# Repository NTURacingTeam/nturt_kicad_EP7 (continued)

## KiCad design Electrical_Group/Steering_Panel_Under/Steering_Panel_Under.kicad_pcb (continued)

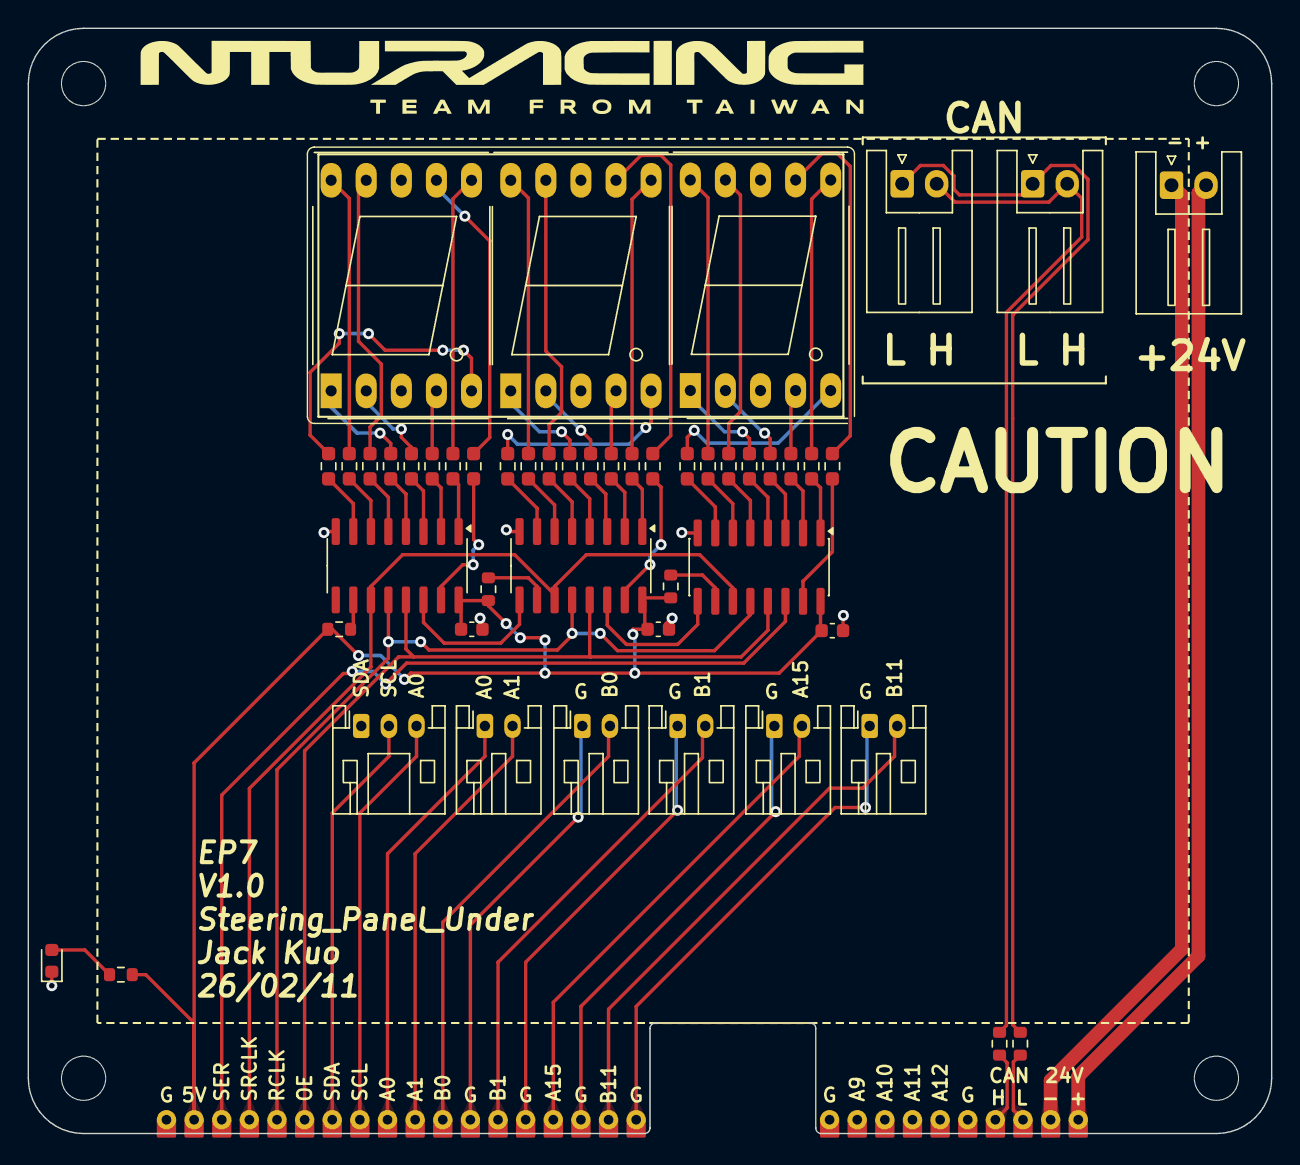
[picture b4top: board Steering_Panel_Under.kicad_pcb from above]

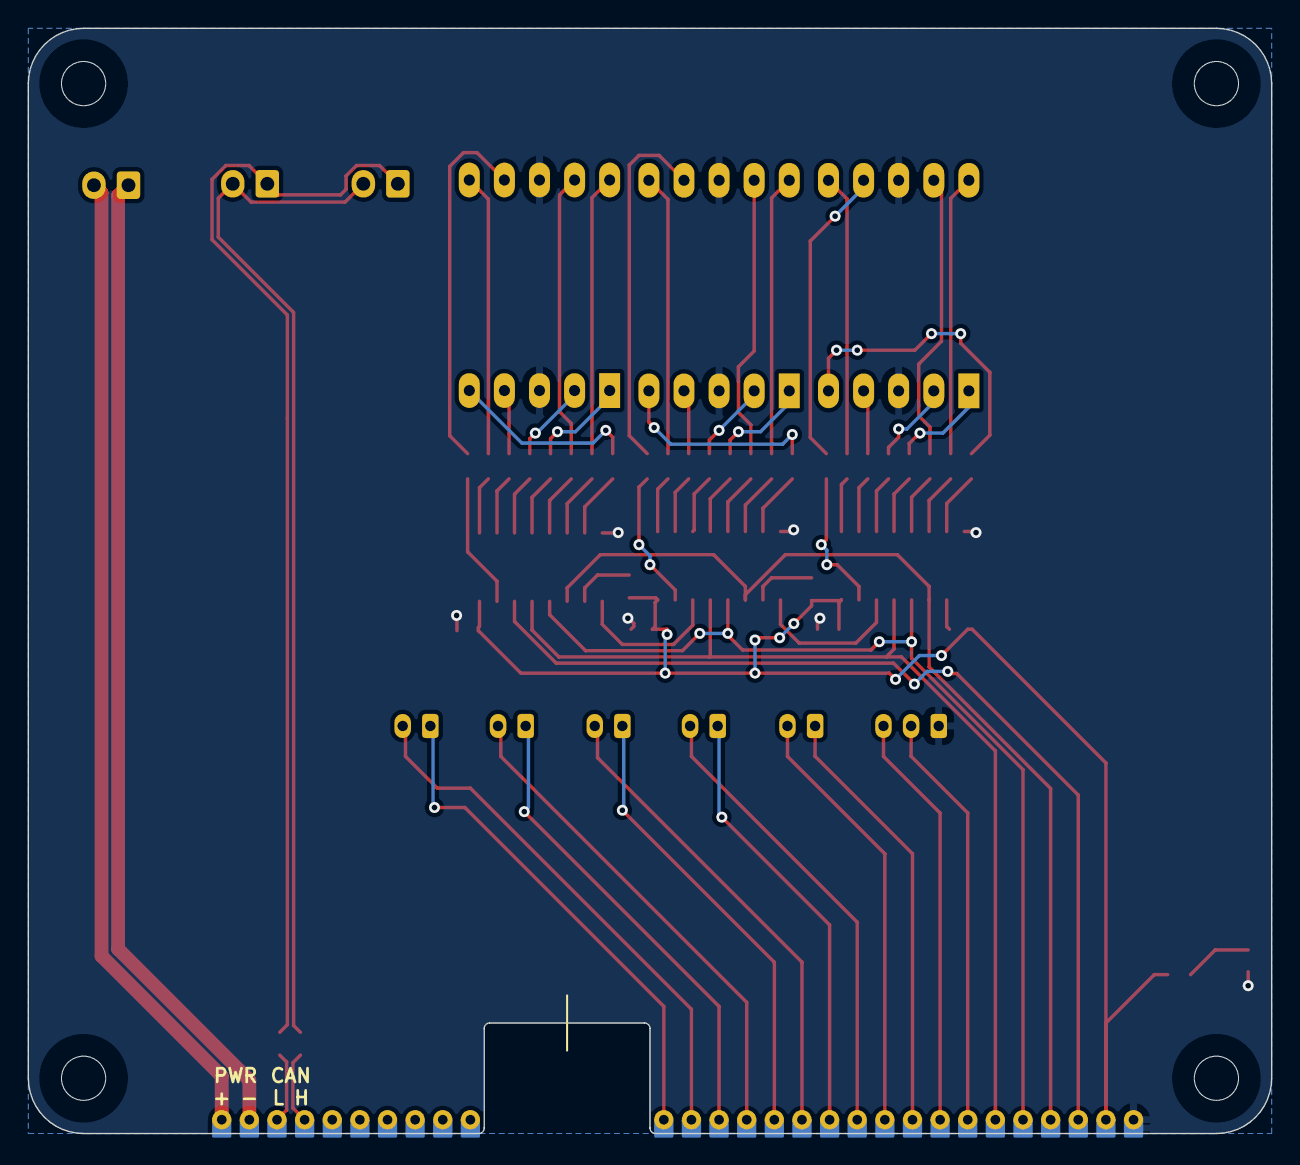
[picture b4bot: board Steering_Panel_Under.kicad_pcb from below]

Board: 2 copper layers, 90.0 x 80.0 mm, 81 parts (2 on the bottom side), 78 nets.

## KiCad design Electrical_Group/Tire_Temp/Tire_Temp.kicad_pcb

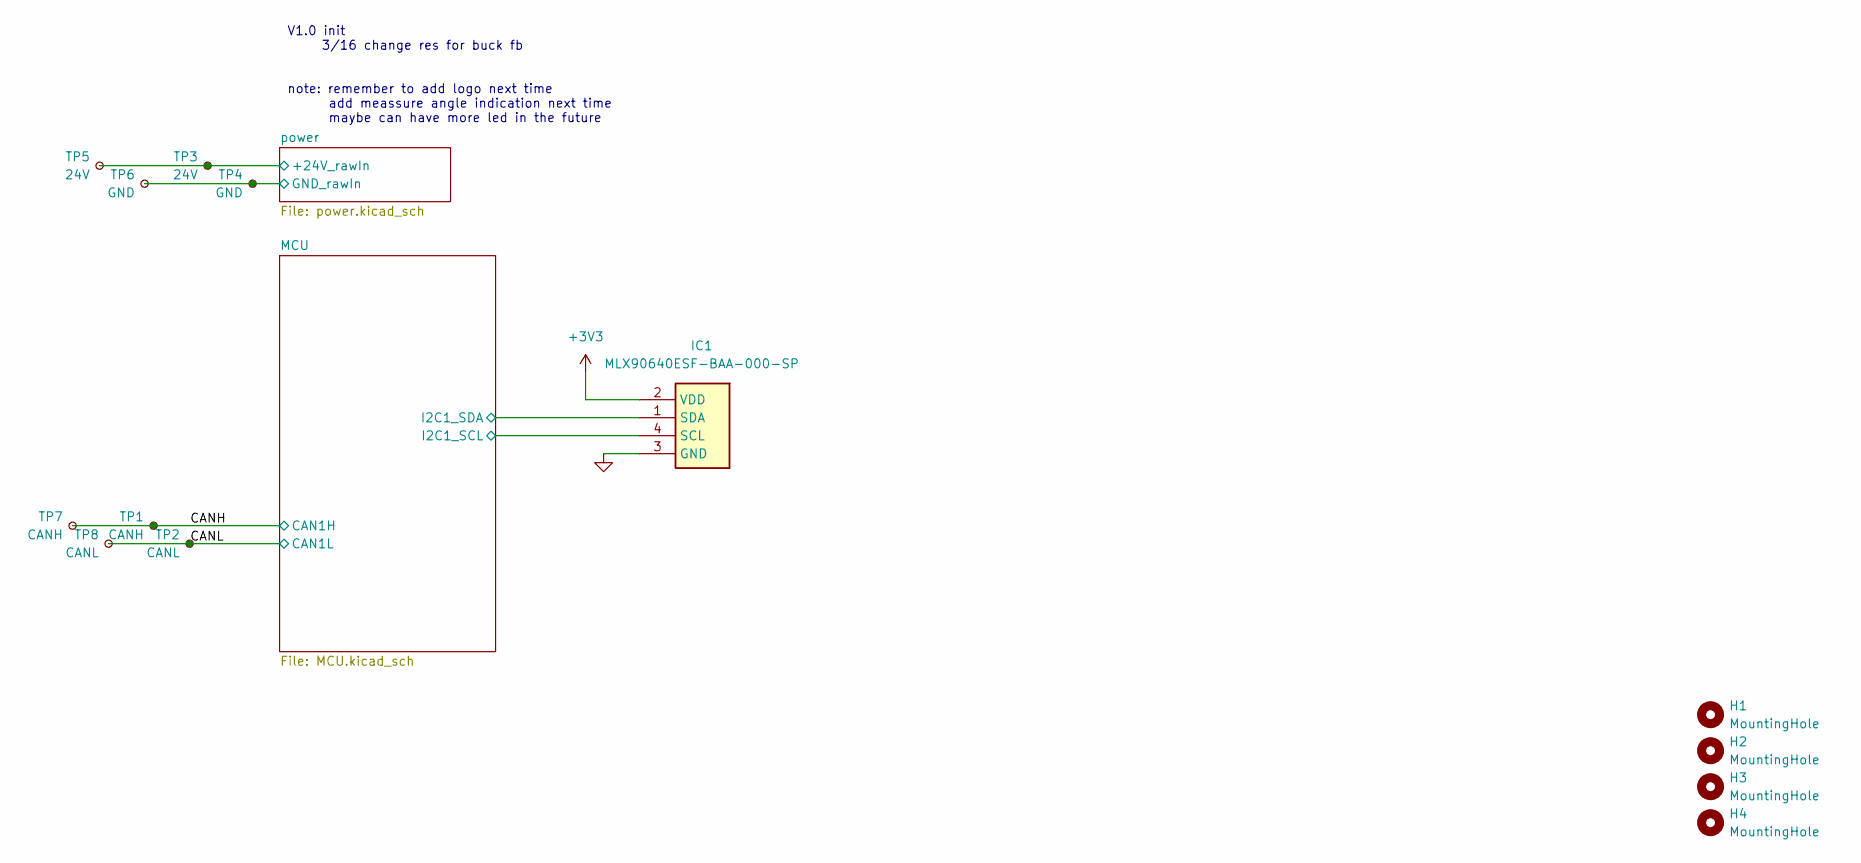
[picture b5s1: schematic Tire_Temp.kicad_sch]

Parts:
H1, H2, H3, H4: MountingHole; MountingHole_3.2mm_M3
IC1: MLX90640ESF-BAA-000-SP; MLX90640ESFBAA000TU; Mouser Part Number 482-MLX90640ESFBAASP
TP1, TP7: CANH; edge_pad_1.4mm_0.7mm
TP2, TP8: CANL; edge_pad_1.4mm_0.7mm
TP3, TP5: 24V; edge_pad_1.4mm_0.7mm
TP4, TP6: GND; edge_pad_1.4mm_0.7mm

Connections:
+3V3: IC1.2 (VDD); also elsewhere on the board
/CANH: TP1.1, TP7.1; also elsewhere on the board
/CANL: TP2.1, TP8.1; also elsewhere on the board
/MCU/I2C1_SCL: IC1.4 (SCL); also elsewhere on the board
/MCU/I2C1_SDA: IC1.1 (SDA); also elsewhere on the board
/power/+24V_rawIn: TP3.1, TP5.1; also elsewhere on the board
GND: IC1.3 (GND), TP4.1, TP6.1; also elsewhere on the board

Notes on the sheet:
V1.0 init 3/16 change res for buck fb note: remember to add logo next time add meassure angle indication next time maybe can have more led in the future

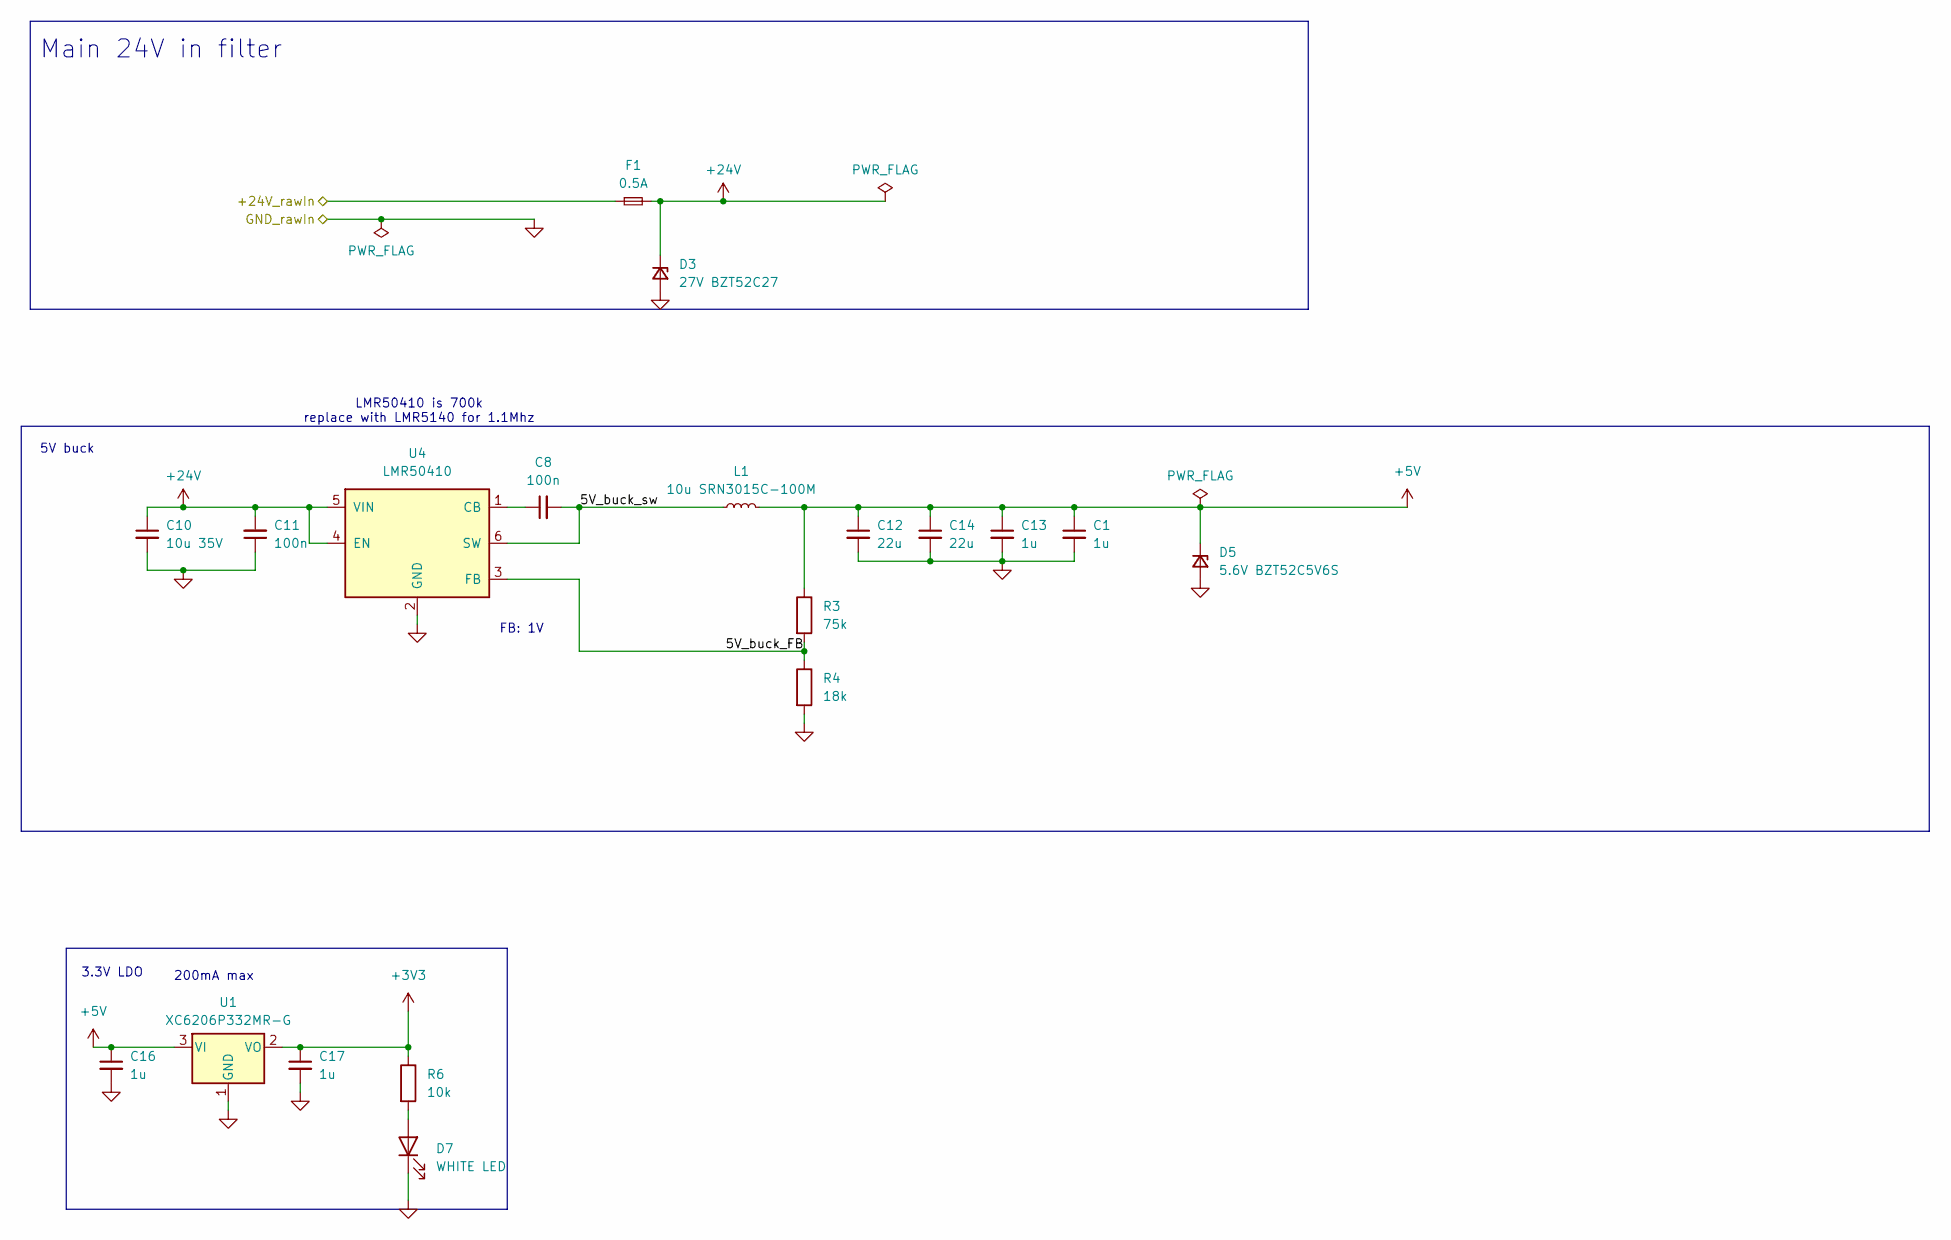
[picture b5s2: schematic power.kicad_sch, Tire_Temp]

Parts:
C1, C13: 1u; C_0805_2012Metric
C8: 100n; C_0402_1005Metric
C10: 10u 35V; C_1206_3216Metric
C11: 100n; C_0603_1608Metric
C12, C14: 22u; C_1206_3216Metric
C16, C17: 1u; C_0603_1608Metric
D3: 27V BZT52C27; D_SOD-323
D5: 5.6V BZT52C5V6S; D_SOD-323
D7: WHITE LED; LED_0603_1608Metric
F1: 0.5A; Fuse_1206_3216Metric
L1: 10u SRN3015C-100M; SRN3015C
R3: 75k; R_0402_1005Metric
R4: 18k; R_0402_1005Metric
R6: 10k; R_0402_1005Metric
U1: XC6206P332MR-G; SOT-23-3
U4: LMR50410; SOT-23-6

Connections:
+3V3: C17.1, R6.1, U1.2 (VO); also elsewhere on the board
+5V: C1.1, C12.1, C13.1, C14.1, C16.1, D5.1 (K), L1.2, R3.1, U1.3 (VI); also elsewhere on the board
+24V: C10.1, C11.2, D3.1 (K), F1.2, U4.4 (EN), U4.5 (VIN)
/power/5V_buck_FB: R3.2, R4.1, U4.3 (FB)
/power/5V_buck_sw: C8.2, L1.1, U4.6 (SW)
/power/+24V_rawIn: F1.1; also elsewhere on the board
GND: C1.2, C10.2, C11.1, C12.2, C13.2, C14.2, C16.2, C17.2, D3.2 (A), D5.2 (A), D7.1 (K), R4.2, U1.1 (GND), U4.2 (GND); also elsewhere on the board
unnamed: D7.2 (A), R6.2
unnamed: C8.1, U4.1 (CB)

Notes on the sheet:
LMR50410 is 700k replace with LMR5140 for 1.1Mhz
FB: 1V
200mA max
5V buck
3.3V LDO
Main 24V in filter

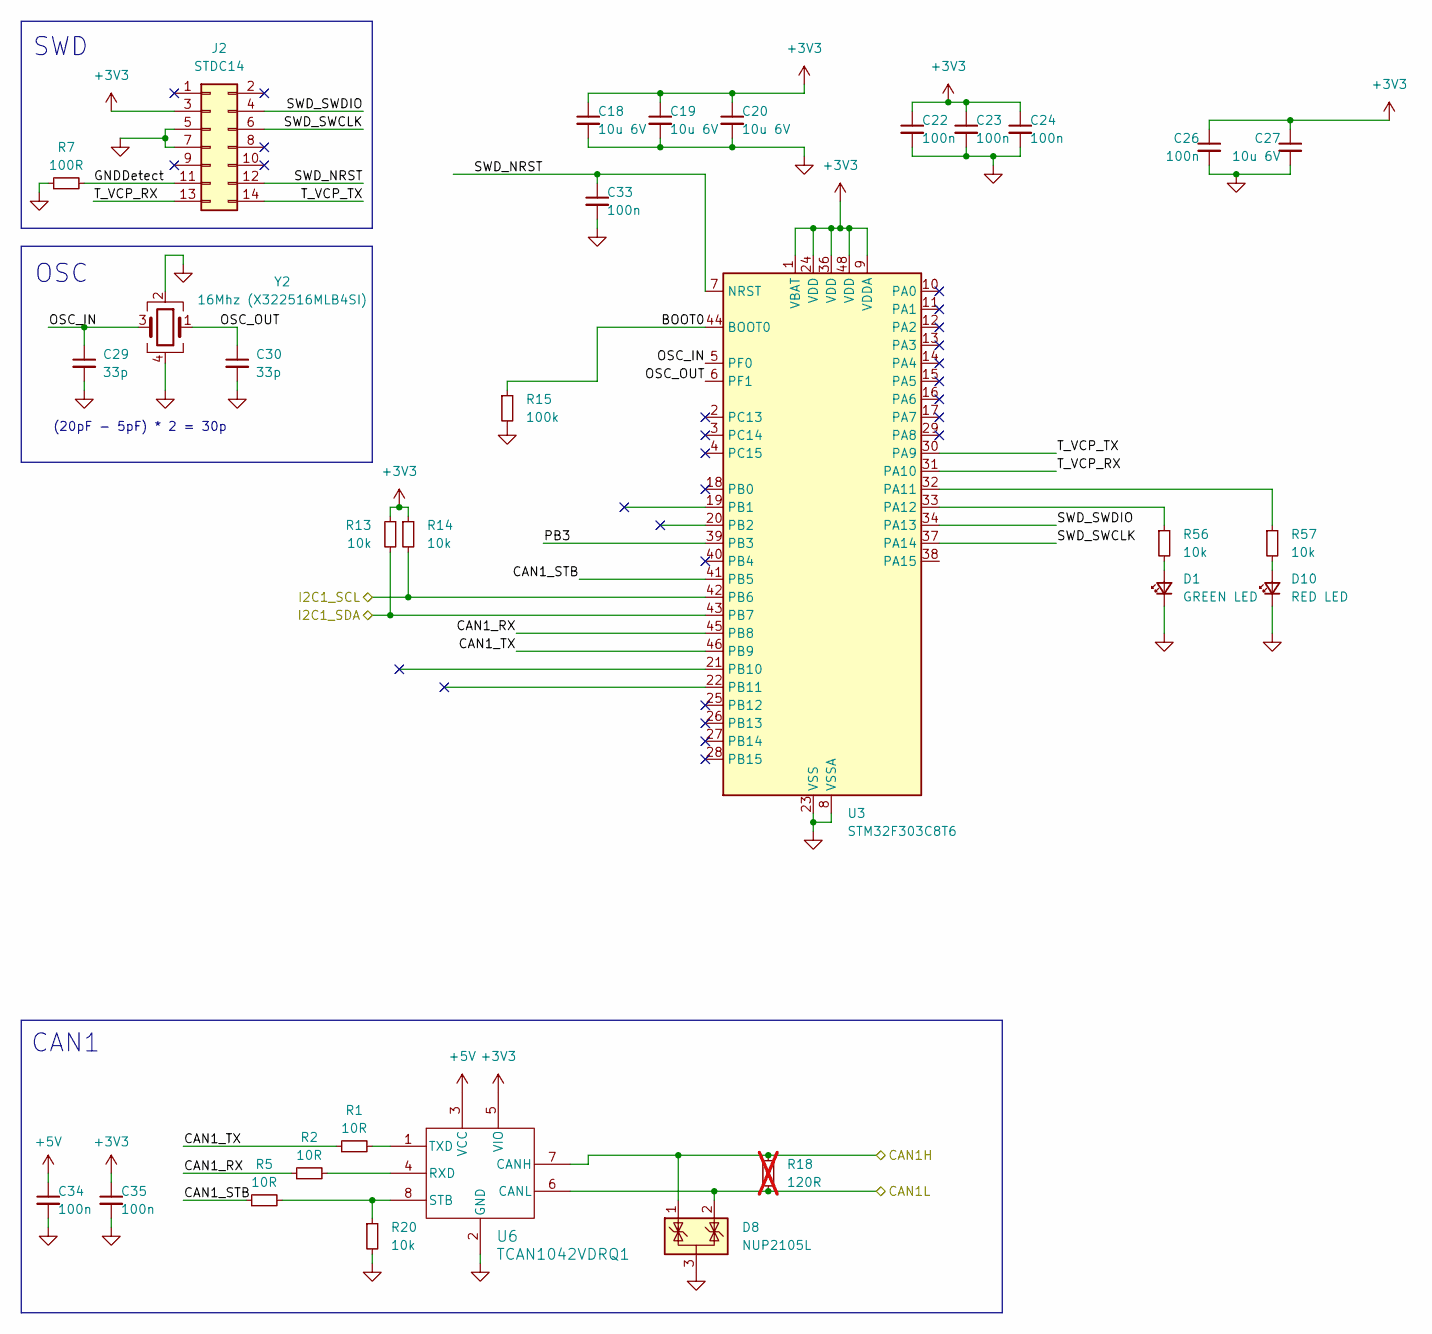
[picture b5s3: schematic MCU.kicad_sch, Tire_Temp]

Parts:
C18, C19, C20, C27: 10u 6V; C_0402_1005Metric
C22, C23, C24, C26, C33, C34, C35: 100n; C_0402_1005Metric
C29, C30: 33p; C_0402_1005Metric
D1: GREEN LED; LED_0603_1608Metric
D8: NUP2105L; SOT-23
D10: RED LED; LED_0603_1608Metric
J2: STDC14; box_header_14P_pitch1.27_smd
R1, R2, R5: 10R; R_0402_1005Metric
R7: 100R; R_0402_1005Metric
R13, R14, R20, R56, R57: 10k; R_0402_1005Metric
R15: 100k; R_0402_1005Metric
R18: 120R; R_0402_1005Metric; not fitted
U3: STM32F303C8T6; LQFP-48_7x7mm_P0.5mm
U6: TCAN1042VDRQ1; SOIC-8_3.9x4.9mm_P1.27mm
Y2: 16Mhz (X322516MLB4SI); Crystal_SMD_3225-4Pin_3.2x2.5mm

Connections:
+3V3: C18.1, C19.1, C20.1, C22.1, C23.1, C24.1, C26.1, C27.1, C35.1, J2.3, R13.1, R14.1, U3.1 (VBAT), U3.9 (VDDA), U3.24 (VDD), U3.36 (VDD), U3.48 (VDD), U6.5 (VIO); also elsewhere on the board
+5V: C34.1, U6.3 (VCC); also elsewhere on the board
/CANH: D8.1 (K), R18.1, U6.7 (CANH); also elsewhere on the board
/CANL: D8.2 (K), R18.2, U6.6 (CANL); also elsewhere on the board
/MCU/BOOT0: R15.1, U3.44 (BOOT0)
/MCU/CAN1_RX: R2.1, U3.45 (PB8)
/MCU/CAN1_STB: R5.1, U3.41 (PB5)
/MCU/CAN1_TX: R1.1, U3.46 (PB9)
/MCU/GNDDetect: J2.11, R7.2
/MCU/I2C1_SCL: R14.2, U3.42 (PB6); also elsewhere on the board
/MCU/I2C1_SDA: R13.2, U3.43 (PB7); also elsewhere on the board
/MCU/OSC_IN: C29.1, U3.5 (PF0), Y2.3
/MCU/OSC_OUT: C30.1, U3.6 (PF1), Y2.1
/MCU/PB3: U3.39 (PB3)
/MCU/SWD_NRST: C33.1, J2.12, U3.7 (NRST)
/MCU/SWD_SWCLK: J2.6, U3.37 (PA14)
/MCU/SWD_SWDIO: J2.4, U3.34 (PA13)
/MCU/T_VCP_RX: J2.13, U3.31 (PA10)
/MCU/T_VCP_TX: J2.14, U3.30 (PA9)
GND: C18.2, C19.2, C20.2, C22.2, C23.2, C24.2, C26.2, C27.2, C29.2, C30.2, C33.2, C34.2, C35.2, D1.1 (K), D8.3 (A), D10.1 (K), J2.5, J2.7, R7.1, R15.2, R20.2, U3.8 (VSSA), U3.23 (VSS), U3.35 (VSS), U3.47 (VSS), U6.2 (GND), Y2.2, Y2.4; also elsewhere on the board
unnamed: D1.2 (A), R56.2
unnamed: D10.2 (A), R57.2
unnamed: R57.1, U3.32 (PA11)
unnamed: R56.1, U3.33 (PA12)
unnamed: R2.2, U6.4 (RXD)
unnamed: R5.2, R20.1, U6.8 (STB)
unnamed: R1.2, U6.1 (TXD)

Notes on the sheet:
SWD
OSC
(20pF - 5pF) * 2 = 30p
CAN1

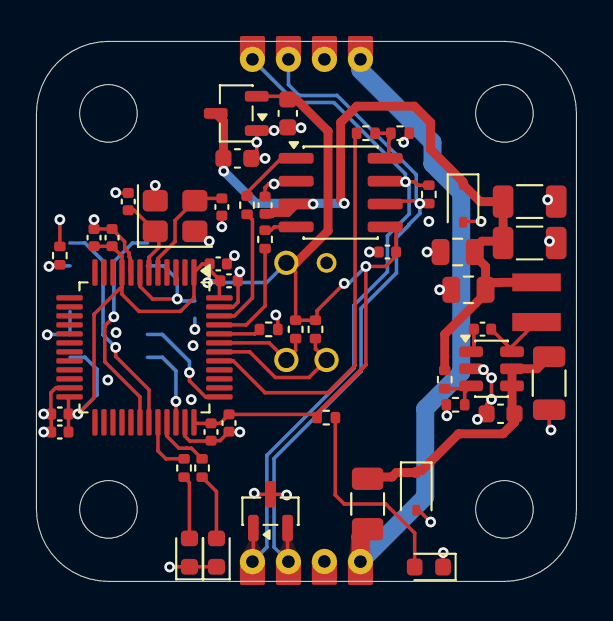
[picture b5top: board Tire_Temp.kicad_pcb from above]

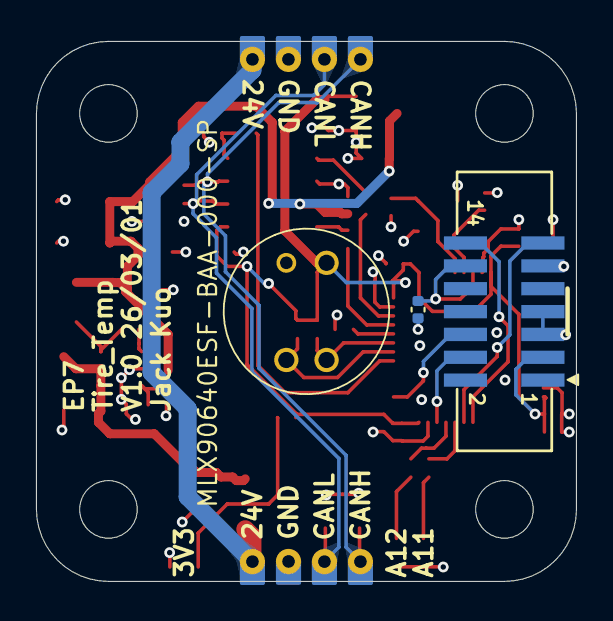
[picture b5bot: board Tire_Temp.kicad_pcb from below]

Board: 4 copper layers, 30.0 x 30.0 mm, 63 parts (3 on the bottom side), 32 nets.

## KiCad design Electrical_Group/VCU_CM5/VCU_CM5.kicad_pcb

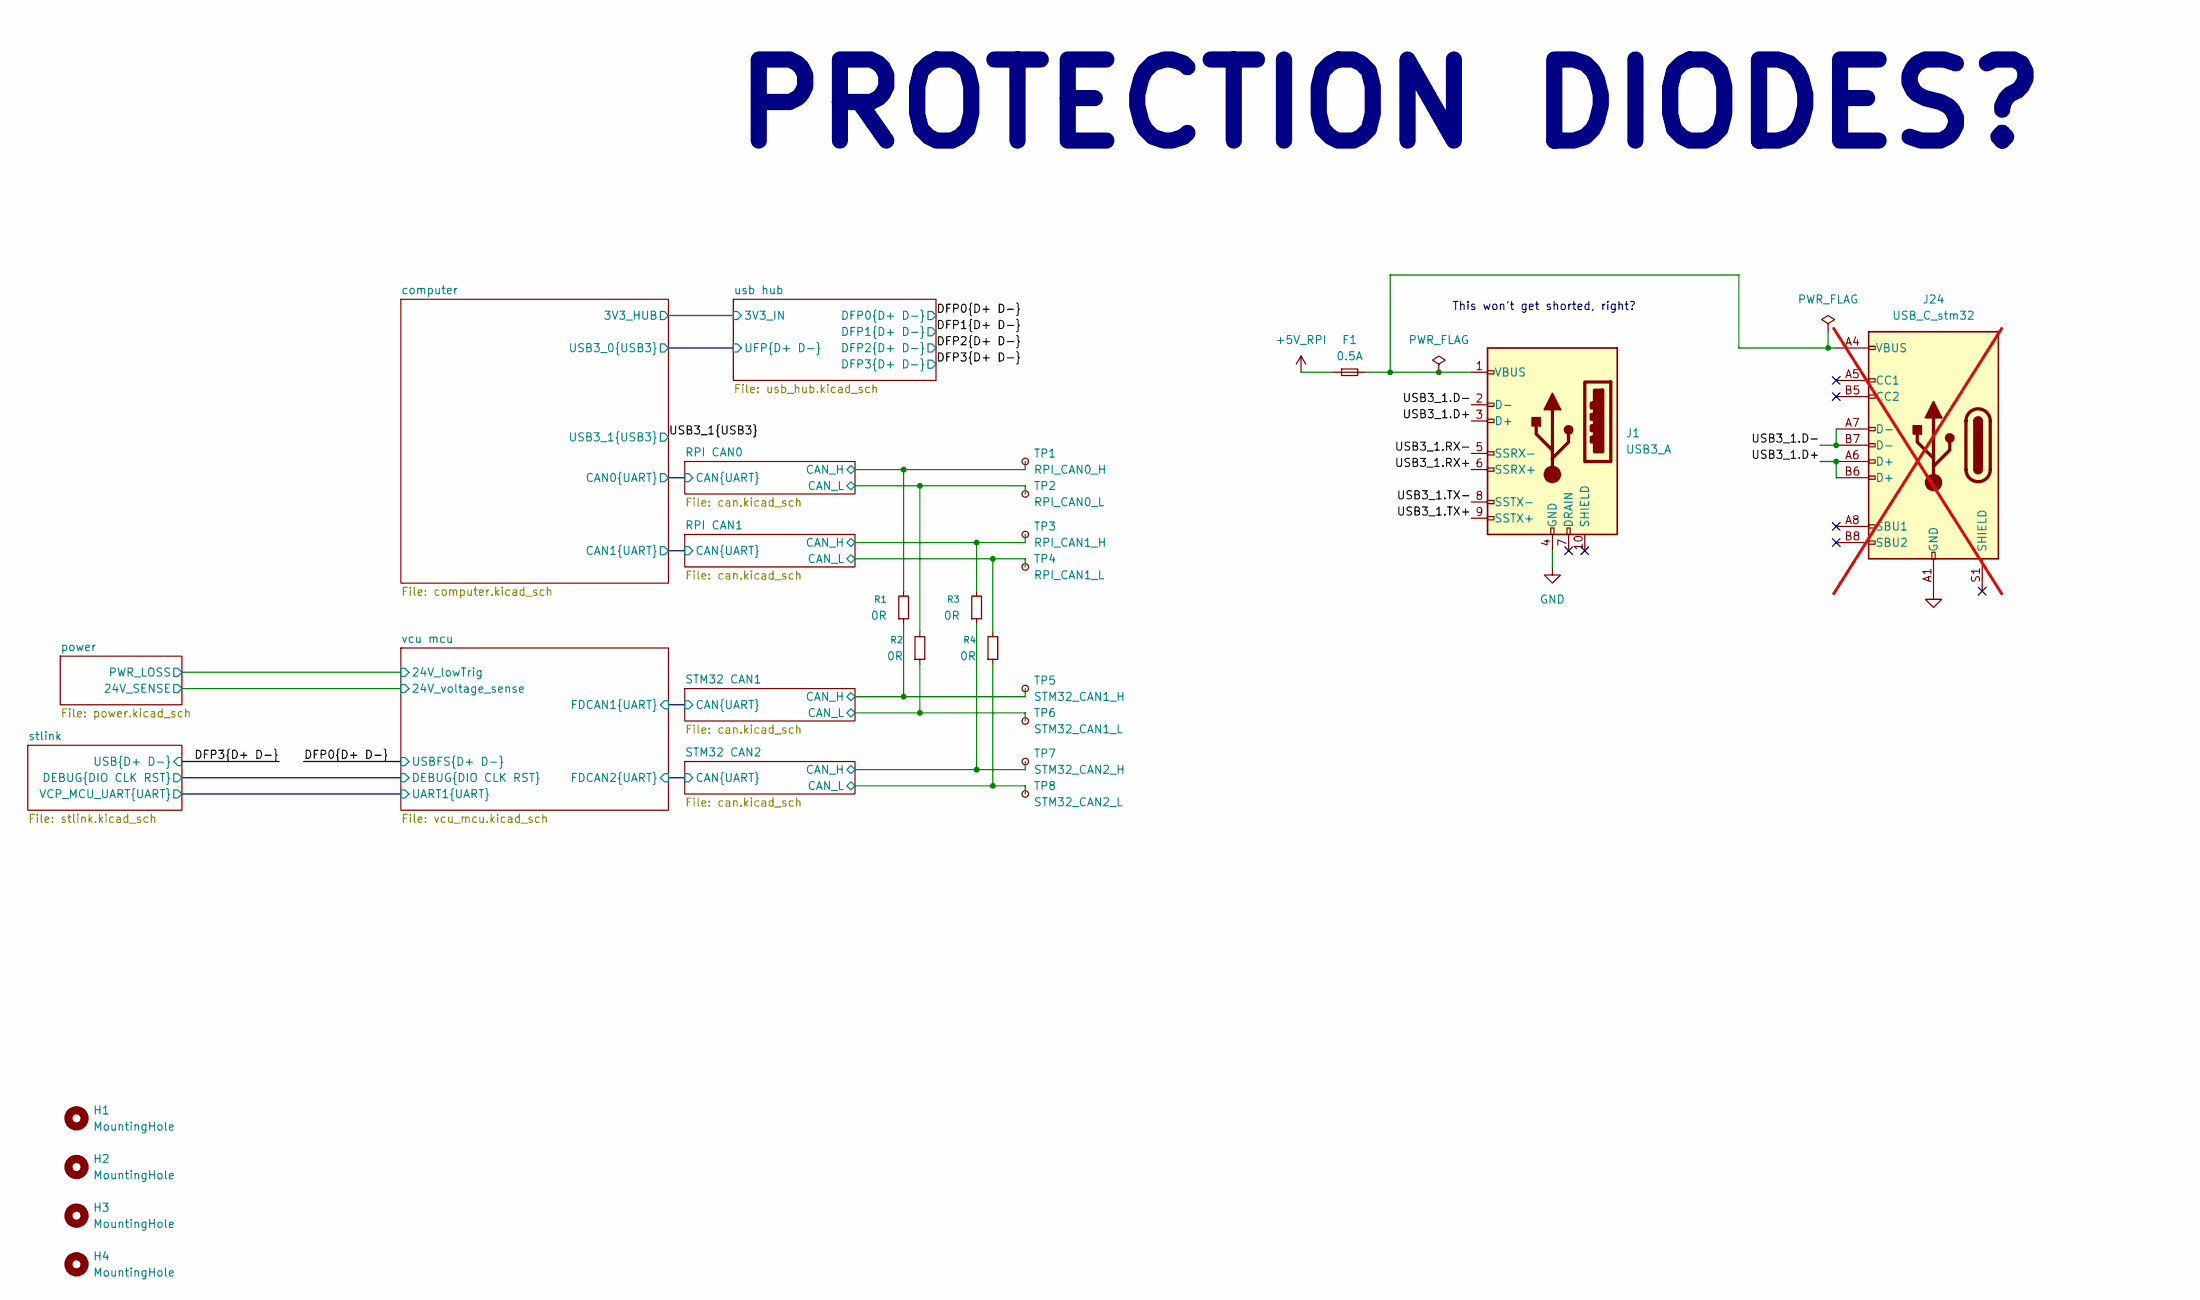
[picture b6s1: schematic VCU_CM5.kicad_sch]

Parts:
F1: 0.5A; Fuse_1206_3216Metric_Pad1.42x1.75mm_HandSolder
H1, H2, H3, H4: MountingHole; MountingHole_3.2mm_M3
J1: USB3_A; USB3_A_Molex_48393-001
J24: USB_C_stm32; USB_C_Receptacle_GCT_USB4105-xx-A_16P_TopMnt_Horizontal; not fitted
R1, R2, R3, R4: 0R; R_0603_1608Metric_Pad0.98x0.95mm_HandSolder
TP1: RPI_CAN0_H; edge_pad_1.4mm_0.7mm
TP2: RPI_CAN0_L; edge_pad_1.4mm_0.7mm
TP3: RPI_CAN1_H; edge_pad_1.4mm_0.7mm
TP4: RPI_CAN1_L; edge_pad_1.4mm_0.7mm
TP5: STM32_CAN1_H; edge_pad_1.4mm_0.7mm
TP6: STM32_CAN1_L; edge_pad_1.4mm_0.7mm
TP7: STM32_CAN2_H; edge_pad_1.4mm_0.7mm
TP8: STM32_CAN2_L; edge_pad_1.4mm_0.7mm

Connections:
+5V_CM: F1.1; also elsewhere on the board
/RPI CAN0/CAN_H: R1.2, TP1.1; also elsewhere on the board
/RPI CAN0/CAN_L: R2.2, TP2.1; also elsewhere on the board
/RPI CAN1/CAN_H: R3.2, TP3.1; also elsewhere on the board
/RPI CAN1/CAN_L: R4.2, TP4.1; also elsewhere on the board
/STM32 CAN1/CAN_H: R1.1, TP5.1; also elsewhere on the board
/STM32 CAN1/CAN_L: R2.1, TP6.1; also elsewhere on the board
/STM32 CAN2/CAN_H: R3.1, TP7.1; also elsewhere on the board
/STM32 CAN2/CAN_L: R4.1, TP8.1; also elsewhere on the board
/USB3_1.D+: J1.3 (D+), J24.A6 (D+), J24.B6 (D+); also elsewhere on the board
/USB3_1.D-: J1.2 (D-), J24.A7 (D-), J24.B7 (D-); also elsewhere on the board
/USB3_1.RX+: J1.6 (SSRX+); also elsewhere on the board
/USB3_1.RX-: J1.5 (SSRX-); also elsewhere on the board
/USB3_1.TX+: J1.9 (SSTX+); also elsewhere on the board
/USB3_1.TX-: J1.8 (SSTX-); also elsewhere on the board
GND: J1.4 (GND), J24.A1 (GND), J24.A12 (GND), J24.B1 (GND), J24.B12 (GND); also elsewhere on the board
unnamed: F1.2, J1.1 (VBUS), J24.A4 (VBUS), J24.A9 (VBUS), J24.B4 (VBUS), J24.B9 (VBUS)

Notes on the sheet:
PROTECTION DIODES?
This won't get shorted, right?

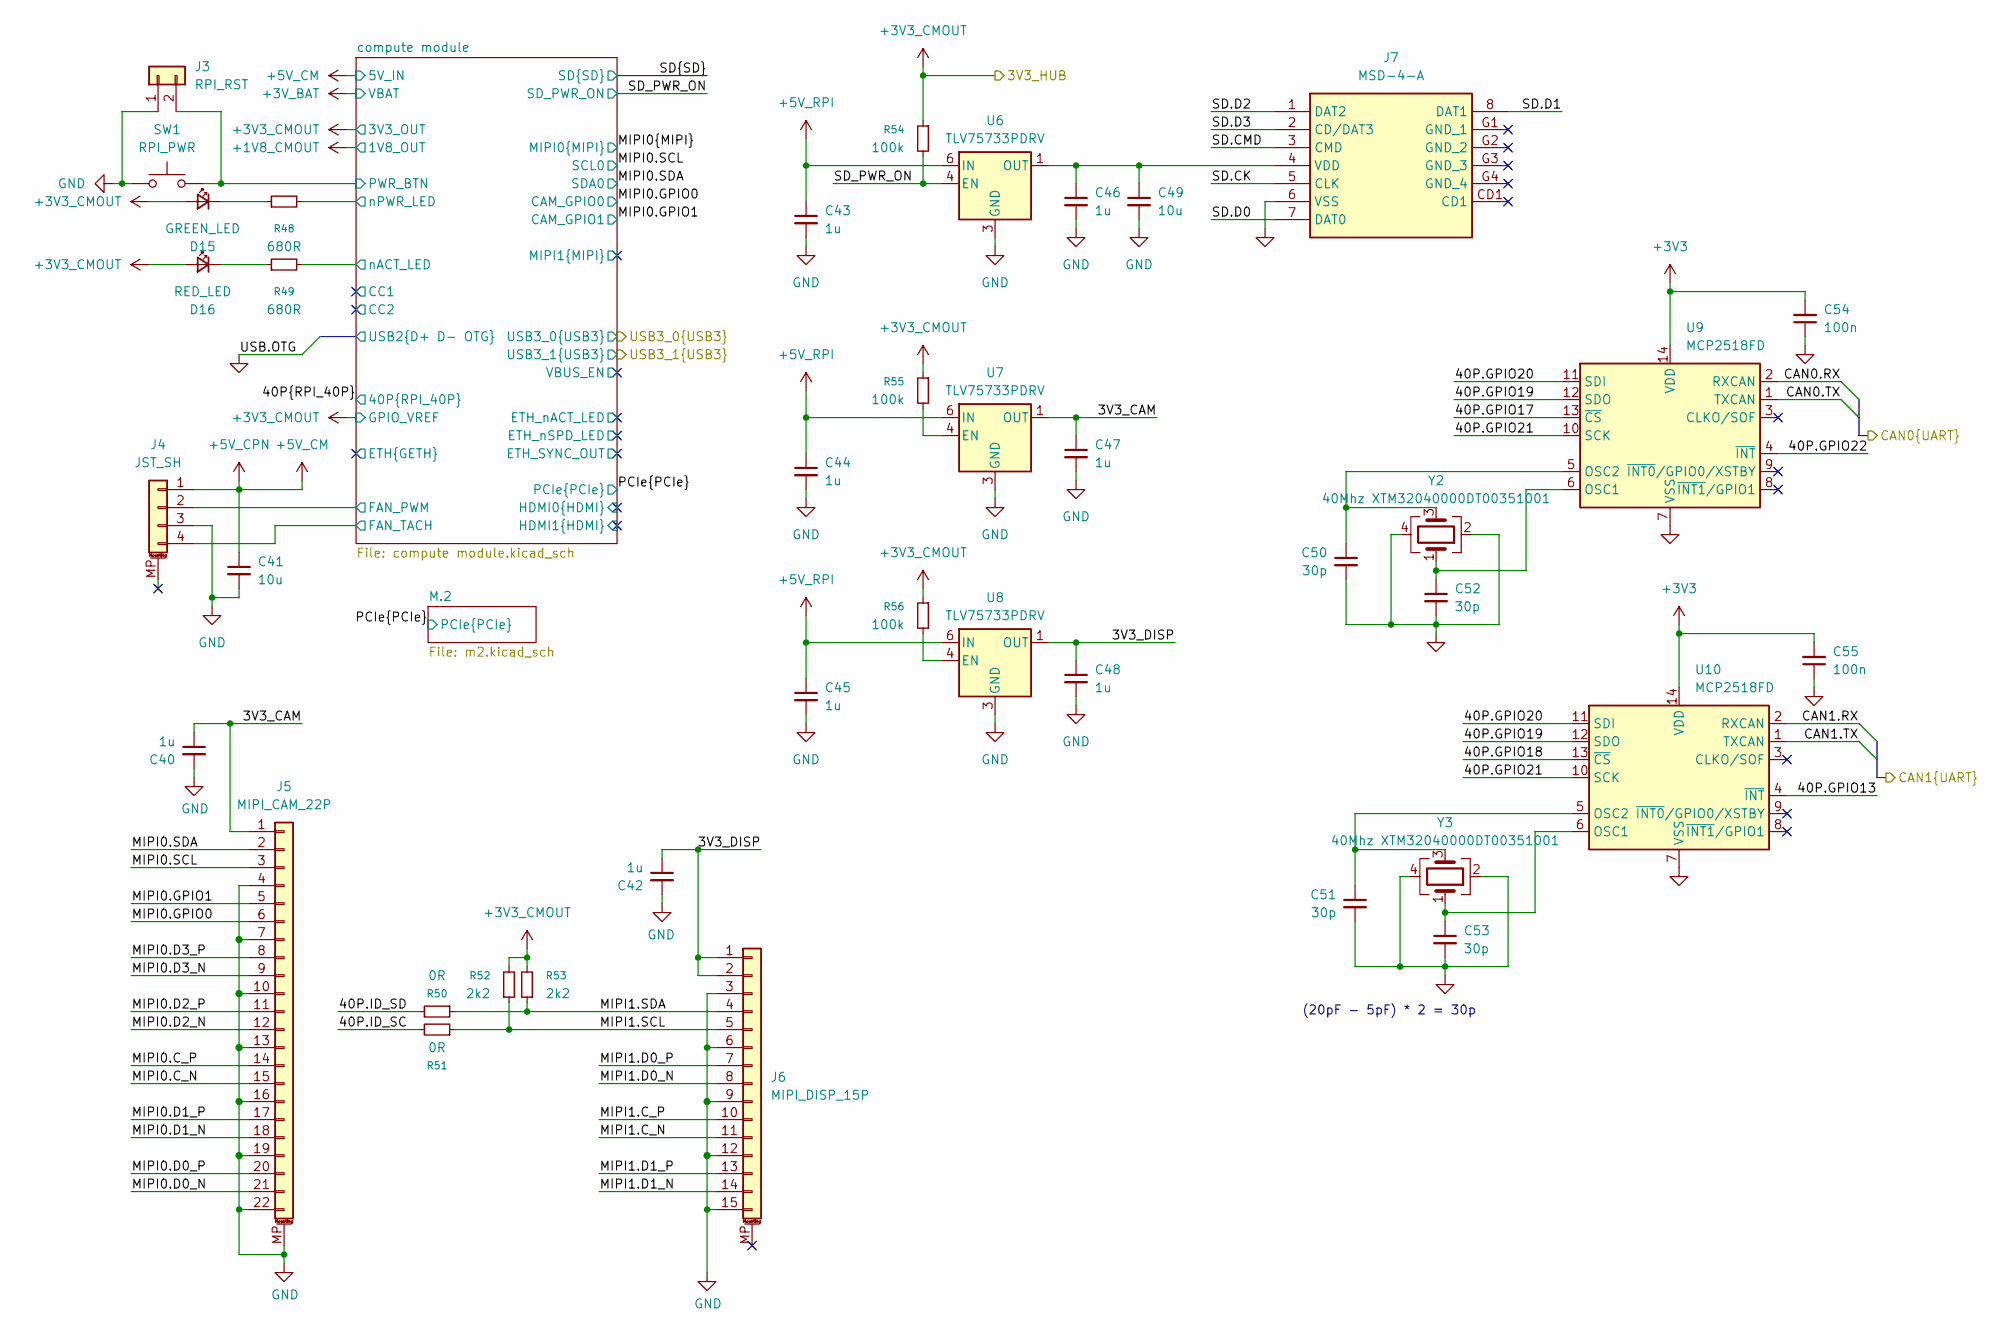
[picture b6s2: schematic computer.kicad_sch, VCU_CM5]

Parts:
C40, C42, C43, C44, C45, C46, C47, C48: 1u; C_0402_1005Metric
C41, C49: 10u; C_0603_1608Metric
C50, C51, C52, C53: 30p; C_0402_1005Metric
C54, C55: 100n; C_0402_1005Metric
D15: GREEN_LED; LED_0603_1608Metric
D16: RED_LED; LED_0603_1608Metric
J3: RPI_RST; PinHeader_1x02_P2.00mm_Horizontal
J4: JST_SH; JST_SH_SM04B-SRSS-TB_1x04-1MP_P1.00mm_Horizontal; Part Description 4 pin vertical 1mm pitch connector
J5: MIPI_CAM_22P; Hirose_FH12-22S-0.5SH_1x22-1MP_P0.50mm_Horizontal; Part Description 22 Position FFC, FPC Connector Contacts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
J6: MIPI_DISP_15P; Molex_200528-0150_1x15-1MP_P1.00mm_Horizontal
J7: MSD-4-A; MSD4A; Mouser Part Number 179-MSD-4-A
R48, R49: 680R; R_0402_1005Metric
R50, R51: 0R; R_0402_1005Metric
R52, R53: 2k2; R_0402_1005Metric
R54, R55, R56: 100k; R_0402_1005Metric
SW1: RPI_PWR; SW_Tactile_SPST_NO_Straight_CK_PTS636Sx25SMTRLFS
U6, U7, U8: TLV75733PDRV; WSON-6-1EP_2x2mm_P0.65mm_EP1x1.6mm
U9, U10: MCP2518FD; SOIC-14_3.9x8.7mm_P1.27mm
Y2, Y3: 40Mhz XTM32040000DT00351001; Crystal_SMD_3225-4Pin_3.2x2.5mm

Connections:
+3V3: C54.2, C55.2, U9.14 (VDD), U10.14 (VDD); also elsewhere on the board
+3V3_CMOUT: D15.2 (A), D16.2 (A), R52.2, R53.2, R54.1, R55.1, R56.1; also elsewhere on the board
+5V_CM: C41.1, C43.1, C44.1, C45.1, J4.1, U6.6 (IN), U7.6 (IN), U8.6 (IN); also elsewhere on the board
/RPI CAN0/CAN.RX: U9.2 (RXCAN); also elsewhere on the board
/RPI CAN0/CAN.TX: U9.1 (TXCAN); also elsewhere on the board
/RPI CAN1/CAN.RX: U10.2 (RXCAN); also elsewhere on the board
/RPI CAN1/CAN.TX: U10.1 (TXCAN); also elsewhere on the board
/computer/3V3_CAM: C40.1, C47.1, J5.1, U7.1 (OUT)
/computer/3V3_DISP: C42.1, C48.1, J6.1, J6.2, U8.1 (OUT)
/computer/40P.GPIO13: U10.4 (~INT); also elsewhere on the board
/computer/40P.GPIO17: U9.13 (~CS); also elsewhere on the board
/computer/40P.GPIO18: U10.13 (~CS); also elsewhere on the board
/computer/40P.GPIO19: U9.12 (SDO), U10.12 (SDO); also elsewhere on the board
/computer/40P.GPIO20: U9.11 (SDI), U10.11 (SDI); also elsewhere on the board
/computer/40P.GPIO21: U9.10 (SCK), U10.10 (SCK); also elsewhere on the board
/computer/40P.GPIO22: U9.4 (~INT); also elsewhere on the board
/computer/40P.ID_SC: R51.2; also elsewhere on the board
/computer/40P.ID_SD: R50.2; also elsewhere on the board
/computer/MIPI0.C_N: J5.15; also elsewhere on the board
/computer/MIPI0.C_P: J5.14; also elsewhere on the board
/computer/MIPI0.D0_N: J5.21; also elsewhere on the board
/computer/MIPI0.D0_P: J5.20; also elsewhere on the board
/computer/MIPI0.D1_N: J5.18; also elsewhere on the board
/computer/MIPI0.D1_P: J5.17; also elsewhere on the board
/computer/MIPI0.D2_N: J5.12; also elsewhere on the board
/computer/MIPI0.D2_P: J5.11; also elsewhere on the board
/computer/MIPI0.D3_N: J5.9; also elsewhere on the board
/computer/MIPI0.D3_P: J5.8; also elsewhere on the board
/computer/MIPI0.GPIO0: J5.6; also elsewhere on the board
/computer/MIPI0.GPIO1: J5.5; also elsewhere on the board
/computer/MIPI0.SCL: J5.3; also elsewhere on the board
/computer/MIPI0.SDA: J5.2; also elsewhere on the board
/computer/MIPI1.SCL: J6.5, R51.1, R52.1
/computer/MIPI1.SDA: J6.4, R50.1, R53.1
/computer/SD.CK: J7.5 (CLK); also elsewhere on the board
/computer/SD.CMD: J7.3 (CMD); also elsewhere on the board
/computer/SD.D0: J7.7 (DAT0); also elsewhere on the board
/computer/SD.D1: J7.8 (DAT1); also elsewhere on the board
/computer/SD.D2: J7.1 (DAT2); also elsewhere on the board
/computer/SD.D3: J7.2 (CD/DAT3); also elsewhere on the board
/computer/SD_PWR_ON: R54.2, U6.4 (EN); also elsewhere on the board
/computer/compute module/FAN_PWM: J4.2; also elsewhere on the board
/computer/compute module/FAN_TACH: J4.4; also elsewhere on the board
/computer/compute module/MIPI1.C_N: J6.11; also elsewhere on the board
/computer/compute module/MIPI1.C_P: J6.10; also elsewhere on the board
/computer/compute module/MIPI1.D0_N: J6.8; also elsewhere on the board
/computer/compute module/MIPI1.D0_P: J6.7; also elsewhere on the board
/computer/compute module/MIPI1.D1_N: J6.14; also elsewhere on the board
/computer/compute module/MIPI1.D1_P: J6.13; also elsewhere on the board
/computer/compute module/PWR_BTN: J3.2, SW1.1; also elsewhere on the board
/computer/compute module/nACT_LED: R49.2; also elsewhere on the board
/computer/compute module/nPWR_LED: R48.2; also elsewhere on the board
GND: C40.2, C41.2, C42.2, C43.2, C44.2, C45.2, C46.2, C47.2, C48.2, C49.2, C50.2, C51.2, C52.2, C53.2, C54.1, C55.1, J3.1, J4.3, J5.4, J5.7, J5.10, J5.13, J5.16, J5.19, J5.22, J5.MP (MountPin), J6.3, J6.6, J6.9, J6.12, J6.15, J7.6 (VSS), SW1.2, U6.3 (GND), U6.7 (GND), U7.3 (GND), U7.7 (GND), U8.3 (GND), U8.7 (GND), U9.7 (VSS), U10.7 (VSS), Y2.2, Y2.4, Y3.2, Y3.4; also elsewhere on the board
unnamed: D15.1 (K), R48.1
unnamed: D16.1 (K), R49.1
unnamed: C46.1, C49.1, J7.4 (VDD), U6.1 (OUT)
unnamed: R55.2, U7.4 (EN)
unnamed: R56.2, U8.4 (EN)
unnamed: C52.1, U9.6 (OSC1), Y2.1
unnamed: C50.1, U9.5 (OSC2), Y2.3
unnamed: C53.1, U10.6 (OSC1), Y3.1
unnamed: C51.1, U10.5 (OSC2), Y3.3

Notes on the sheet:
(20pF - 5pF) * 2 = 30p
